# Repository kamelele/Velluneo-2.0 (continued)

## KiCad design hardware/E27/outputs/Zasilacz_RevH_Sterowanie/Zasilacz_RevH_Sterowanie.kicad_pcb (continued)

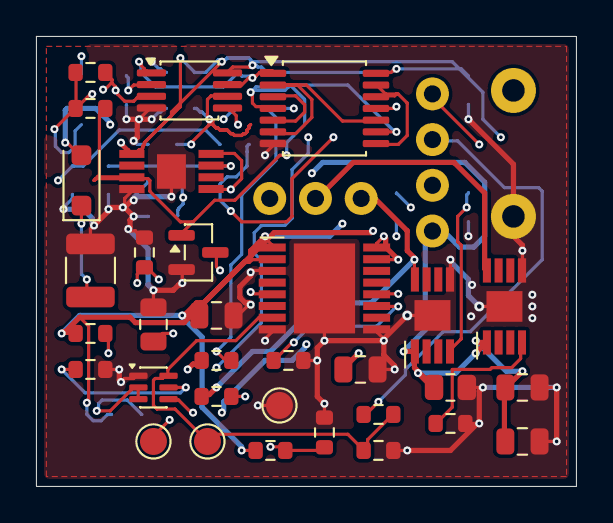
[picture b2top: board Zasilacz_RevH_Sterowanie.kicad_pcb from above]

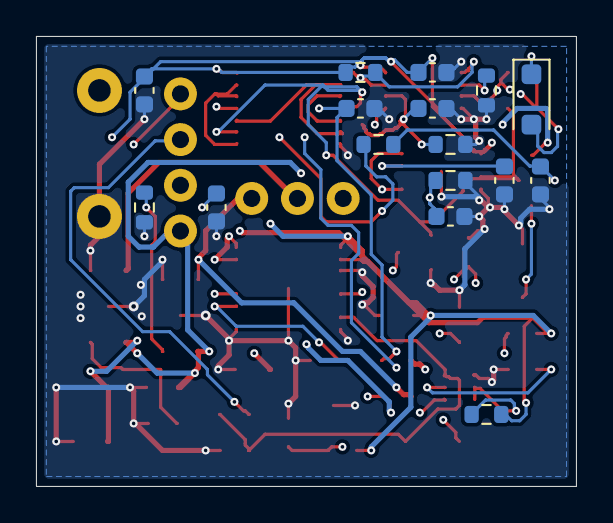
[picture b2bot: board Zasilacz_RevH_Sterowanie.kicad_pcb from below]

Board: 4 copper layers, 30.0 x 25.0 mm, 51 parts (16 on the bottom side), 29 nets.

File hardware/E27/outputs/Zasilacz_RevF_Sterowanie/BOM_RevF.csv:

Ref,Wartość,MPN,Footprint,LCSC Part #,Źródło
U2,TPS26600PWPR,TPS26600PWPR,E27:PWP0016A,C544399,https://jlcpcb.com/partdetail/TexasInstruments-TPS26600PWPR/C544399
C11,100n / 50V,GRM21BR71H104KA01L,Capacitor_SMD:C_0805_2012Metric,C77082,https://jlcpcb.com/partdetail/MurataElectronics-GRM21BR71H10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
R14,226k 0.1%,ERA-3AEB2263V,Resistor_SMD:R_0603_1608Metric,C2075582,https://www.lcsc.com/product-detail/C2075582.html
R15,10k 0.1%,ERA-3AEB103V,Resistor_SMD:R_0603_1608Metric,C190610,https://jlcpcb.com/partdetail/PANASONIC-ERA3AEB103V/C190610
R16,30.1k 1%,ERJ-3EKF3012V,Resistor_SMD:R_0603_1608Metric,C403145,https://www.lcsc.com/product-detail/C403145.html
C12,47n,CC0603KRX7R9BB473,Capacitor_SMD:C_0603_1608Metric,C107093,https://www.lcsc.com/product-detail/C107093.html
R17,10k,ERJ-3EKF1002V,Resistor_SMD:R_0603_1608Metric,C191124,https://www.lcsc.com/product-detail/C191124.html
R18,10k,ERJ-3EKF1002V,Resistor_SMD:R_0603_1608Metric,C191124,https://www.lcsc.com/product-detail/C191124.html
R19,10k,ERJ-6ENF1002V,Resistor_SMD:R_0805_2012Metric,C169253,https://www.lcsc.com/product-detail/C169253.html
C13,100n / 50V,GRM21BR71H104KA01L,Capacitor_SMD:C_0805_2012Metric,C77082,https://jlcpcb.com/partdetail/MurataElectronics-GRM21BR71H10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
J2,S1+TH / S2,,E27:Harness_4pos,,
J3,A+ / KA / KB,,E27:Harness_3pos,,
U3,AL5812MP-13,AL5812MP-13,E27:E27_Al5812_MSOP,C460648,https://www.lcsc.com/product-detail/C460648.html
R20,5.90k 1%,ERJ-3EKF5901V,Resistor_SMD:R_0603_1608Metric,C403290,https://www.lcsc.com/product-detail/C403290.html
C14,100n / 50V,GRM21BR71H104KA01L,Capacitor_SMD:C_0805_2012Metric,C77082,https://jlcpcb.com/partdetail/MurataElectronics-GRM21BR71H10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
U4,AL5812MP-13,AL5812MP-13,E27:E27_Al5812_MSOP,C460648,https://www.lcsc.com/product-detail/C460648.html
R21,5.90k 1%,ERJ-3EKF5901V,Resistor_SMD:R_0603_1608Metric,C403290,https://www.lcsc.com/product-detail/C403290.html
C15,100n / 50V,GRM21BR71H104KA01L,Capacitor_SMD:C_0805_2012Metric,C77082,https://jlcpcb.com/partdetail/MurataElectronics-GRM21BR71H10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
J102,26 V / RTN,,E27:Harness_26V_RTN,,
U101,TPS7A1633,TPS7A1633DGNR,E27:TPS7A16_DGN,C181239,https://www.lcsc.com/product-detail/C181239.html
U102,TLV1702,TLV1702AIDGKR,Package_SO:MSOP-8_3x3mm_P0.65mm,C2870937,https://jlcpcb.com/partdetail/TexasInstruments-TLV1702AIDGKR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
U103,74LVC132A,"74LVC132APW,118",Package_SO:TSSOP-14_4.4x5mm_P0.65mm,C548102,https://jlcpcb.com/partdetail/Nexperia-74LVC132APW118/C548102
D102,PMEG6010CEH,PMEG6010CEH-QX,Diode_SMD:D_SOD-123F,C5311567,https://www.lcsc.com/product-detail/C5311567.html
D103,PMEG6010CEH,PMEG6010CEH-QX,Diode_SMD:D_SOD-123F,C5311567,https://www.lcsc.com/product-detail/C5311567.html
R101,22k,ERJ-3EKF2202V,Resistor_SMD:R_0603_1608Metric,C278611,https://www.lcsc.com/product-detail/C278611.html
R102,2.2k,ERJ-3EKF2201V,Resistor_SMD:R_0603_1608Metric,C116387,https://jlcpcb.com/partdetail/PANASONIC-ERJ3EKF2201V/C116387
R103,133k 0.1%,ERA-3AEB1333V,Resistor_SMD:R_0603_1608Metric,C2087399,https://www.lcsc.com/product-detail/C2087399.html
R104,22k 0.1%,ERA-3AEB223V,Resistor_SMD:R_0603_1608Metric,C445636,https://www.lcsc.com/product-detail/C445636.html
R105,330k 0.1%,RT0603BRD07330KL,Resistor_SMD:R_0603_1608Metric,C861327,https://www.lcsc.com/product-detail/C861327.html
R106,22k 0.1%,ERA-3AEB223V,Resistor_SMD:R_0603_1608Metric,C445636,https://www.lcsc.com/product-detail/C445636.html
R107,330k 0.1%,RT0603BRD07330KL,Resistor_SMD:R_0603_1608Metric,C861327,https://www.lcsc.com/product-detail/C861327.html
R108,22k 0.1%,ERA-3AEB223V,Resistor_SMD:R_0603_1608Metric,C445636,https://www.lcsc.com/product-detail/C445636.html
R109,22k,ERJ-3EKF2202V,Resistor_SMD:R_0603_1608Metric,C278611,https://www.lcsc.com/product-detail/C278611.html
R110,10k 1%,ERJ-3EKF1002V,Resistor_SMD:R_0603_1608Metric,C191124,https://www.lcsc.com/product-detail/C191124.html
R111,100k 1%,ERJ-3EKF1003V,Resistor_SMD:R_0603_1608Metric,C189597,https://www.lcsc.com/product-detail/C189597.html
R112,100k 1%,ERJ-3EKF1003V,Resistor_SMD:R_0603_1608Metric,C189597,https://www.lcsc.com/product-detail/C189597.html
C101,2.2u / 100V,C3225X7R2A225K230AB,Capacitor_SMD:C_1210_3225Metric,C2167827,https://www.lcsc.com/product-detail/C2167827.html
C102,10u / 25V,GRM21BC71E106KE11L,Capacitor_SMD:C_0805_2012Metric,C109040,https://www.lcsc.com/product-detail/C109040.html
C103,10n,CC0603KRX7R9BB103,Capacitor_SMD:C_0603_1608Metric,C100042,https://www.lcsc.com/product-detail/C100042.html
C104,220n / 50V X7R 10%,CGA3E3X7R1H224K080AE,Capacitor_SMD:C_0603_1608Metric,C2171795,https://jlcpcb.com/partdetail/TDK-CGA3E3X7R1H224K080AE/C2171795
C105,220n / 50V X7R 10%,CGA3E3X7R1H224K080AE,Capacitor_SMD:C_0603_1608Metric,C2171795,https://jlcpcb.com/partdetail/TDK-CGA3E3X7R1H224K080AE/C2171795
C106,10n,CC0603KRX7R9BB103,Capacitor_SMD:C_0603_1608Metric,C100042,https://www.lcsc.com/product-detail/C100042.html
C107,100n,C1608X7R1H104K080AE,Capacitor_SMD:C_0603_1608Metric,C2167477,https://jlcpcb.com/partdetail/TDK-C1608X7R1H104K080AE/C2167477
C108,10n,CC0603KRX7R9BB103,Capacitor_SMD:C_0603_1608Metric,C100042,https://www.lcsc.com/product-detail/C100042.html
C109,100n,C1608X7R1H104K080AE,Capacitor_SMD:C_0603_1608Metric,C2167477,https://jlcpcb.com/partdetail/TDK-C1608X7R1H104K080AE/C2167477
R113,100k 1%,ERJ-3EKF1003V,Resistor_SMD:R_0603_1608Metric,C189597,https://www.lcsc.com/product-detail/C189597.html
Q101,MMDT3904,MMDT3904-7-F,Package_TO_SOT_SMD:SOT-363_SC-70-6,C83572,https://www.lcsc.com/product-detail/C83572.html
Q102,2N7002BK,"2N7002BK,215",Package_TO_SOT_SMD:SOT-23,C282405,https://www.lcsc.com/product-detail/C282405.html

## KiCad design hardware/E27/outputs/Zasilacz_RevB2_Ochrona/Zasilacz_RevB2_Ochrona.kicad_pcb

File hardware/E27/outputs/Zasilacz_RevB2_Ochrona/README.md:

# E27 · Rev B2 · moduł prób ochrony zwarciowej

Moduł **50 × 30 mm** do badań części wtórnej zasilacza Rev B1 z izolowanego źródła **18–30 V DC**. Dwa detektory mierzą napięcie na regulatorach prądu. Po wykryciu nadmiernego spadku na jednym z nich przerzutnik utrzymuje blokadę obu kanałów, dopóki układ pomocniczy jest zasilany. Moduł włącza się w powrót S1/TH1 do SHDN.

[Projekt KiCad](Zasilacz_RevB2_Ochrona.kicad_pro) · [Schemat](Zasilacz_RevB2_Ochrona.kicad_sch) · [PCB](Zasilacz_RevB2_Ochrona.kicad_pcb) · [BOM](BOM_RevB2.csv) · [Pliki do przeglądu](Produkcja_DO_PRZEGLADU)

[Schemat do podglądu](Podglady/Zasilacz_RevB2_Ochrona.svg) · [Spód PCB](Podglady/RevB2_dol_3D.png)

## 1. Problem i próg

Przy zwarciu obciążenia AL5812 może nadal ograniczać prąd do około 127 mA. Przy 26 V na regulatorze oznacza to w pierwszej chwili **około 3,3 W**, podczas gdy prąd całego zasilacza może pozostać poniżej progu nadprądowego eFuse. Napięcie K1 lub K2 względem S_RTN odpowiada spadkowi na odpowiednim AL5812, więc mierzymy je niezależnie od prądu eFuse. [Diodes AL5812](https://www.diodes.com/datasheet/download/AL5812.pdf) · [TI TPS26600](https://www.ti.com/lit/ds/symlink/tps2660.pdf)

TLV1702 porównuje napięcie z dzielników 330 kΩ / 22 kΩ z odniesieniem z 3,3 V przez 133 kΩ / 22 kΩ. Kondensatory 220 nF dają około **4,54 ms** nominalnej stałej czasowej. W modelu przyjęto ±27% efektywnej pojemności. Próg nominalny na K1/K2 to **7,49 V**, a model narożnikowy daje **7,15–7,85 V**. Uwzględniono ±2% szyny, ±0,35% osobno dla każdego rezystora, ±5,5 mV offsetu i prądy polaryzacji komparatorów. Tolerancja rezystorów obejmuje ±0,1% początkowo i ±25 ppm/K dla przyjętej zmiany temperatury o 100 K. Dla badanego punktu 26,4 V z obciążeniem 20 V pozostaje około 0,75 V do najniższego obliczonego progu, przed tętnieniami. [TI TLV1702](https://www.ti.com/lit/ds/symlink/tlv1702.pdf) · [TI TPS7A16](https://www.ti.com/lit/ds/symlink/tps7a16.pdf) · [Panasonic ERA 133 kΩ](https://industrial.panasonic.com/ww/products/pt/high-precision-chip-resistors/models/ERA3AEB1333V)

## 2. Sekwencja i współpraca z Rev B1

- TPS7A1633 zasila układ i wystawia sygnał PG po opóźnieniu, typowo około 12 ms dla 10 nF. Zbocze zegara przerzutnika SN74HCS74 jest dodatkowo opóźnione przez RC. PG przez D1 oraz wyjścia komparatora mogą wymusić niski CLR_N. PG i wyjście PERMIT wspólnie sterują PhotoMOS przez bramkę Schmitta. Przed pierwszym załączeniem weryfikować poziomy PG, CLK, CLR_N oraz stan PhotoMOS na wolnych i szybkich rampach. [TI TPS7A16](https://www.ti.com/lit/ds/symlink/tps7a16.pdf) · [TI SN74HCS74](https://www.ti.com/lit/ds/symlink/sn74hcs74.pdf) · [TI SN74LVC1G132](https://www.ti.com/lit/ds/symlink/sn74lvc1g132.pdf)
- Po zdarzeniu niskie CLR_N zeruje PERMIT. Powrót K1/K2 do normalnych wartości ani ponowne zamknięcie S1 nie daje nowego zbocza CLK. Odcięcie utrzymuje się do resetu PG. Głęboki zanik szyny, po którym PG ponownie wzrośnie, może sam ponownie uzbroić układ. To zachowanie jest jawnie objęte próbą.
- PhotoMOS otwiera powrót S1/TH1. Na Rev B1 rezystor R18 ściąga SHDN w dół. R12 modułu dodaje 100 kΩ do istniejących R17/R18, po 10 kΩ, co daje **około 2,17 V** przy 26 V oraz **1,50–2,50 V** przy 18–30 V w modelu bez prądu wejścia SHDN. Bez R12 sam dzielnik daje ok. 13 V przy 26 V. Zalecany zakres wejścia według TI to 0–4 V. Sprawdzić rzeczywiste napięcia oraz pracę styków S1 przy zmniejszonym prądzie. [TI TPS26600, zalecane warunki pracy i opis SHDN](https://www.ti.com/lit/ds/symlink/tps2660.pdf)

### Wiązka J1

1. **S_RAW** z regulowanej szyny przed eFuse.
2. **S_RTN** z masy wtórnej eFuse i regulatorów.
3. **K1** z wyjścia pierwszego regulatora.
4. **K2** z wyjścia drugiego regulatora.
5. **S1_RETURN** z powrotu zamkniętej pętli S1/TH1. Odłączyć ją uprzednio od J2-2.
6. **S_EN** do J2-2 Rev B1. R17 i R18 w tym zestawie mają wartości z Rev B1. S2 i istniejące zabezpieczenie OVP pracują w swoich dotychczasowych torach.

Punkty TP1–TP6 oznaczają odpowiednio S_RTN, 3,3 V, PG, CLR_N, PERMIT i SHDN. Pomiar CLK można wykonać na C8. D3 jest diodą od wyjścia LDO do odseparowanego przez D2 wejścia LDO, która ogranicza napięcie wsteczne przy zaniku. Przy próbach zaniku sprawdzić również (V_{OUT}-V_{IN}) U1 przy rzeczywistych pojemnościach i temperaturze. Dla C2 10 µF dobrać egzemplarz o pojemności efektywnej co najmniej 2,2 µF przy polaryzacji 3,3 V i skrajnej temperaturze. [TI TPS7A16](https://www.ti.com/lit/ds/symlink/tps7a16.pdf) · [TDK C1](https://product.tdk.com/en/search/capacitor/ceramic/mlcc/info?part_no=C3225X7R2A225K230AB)

## 3. Model i wynik kontroli

- Model RC przewiduje decyzję komparatora po **1,06–2,08 ms** dla idealnego skoku 0→26 V i **4,14–8,88 ms** dla 0→10 V. Czas odłączenia prądu obejmuje dodatkowo PhotoMOS, TPS26600 i rozładowanie pojemności. Panasonic podaje do 0,5 ms wyłączenia AQY212GS w swoich warunkach 25°C, z prądem wejścia 5 mA i obciążeniem 100 mA. W pętli SHDN warunki są inne. [Panasonic AQY212GS](https://industry.panasonic.com/ac/cdn/e/control/relay/photomos/catalog/semi_eng_gu1a_aqy21_gs.pdf)
- [Wyniki 18 przypadków modelowych](Model_RevB2_przypadki.csv) obejmują dwa narożniki, zwarcia osobno na K1 i K2, zwarcie przy włączeniu, impulsy, otwartą pętlę S1 i ponowne uzbrojenie po utracie PG. Wydłużenie filtra z początkowych 47 nF do 220 nF pozwoliło w obu badanych narożnikach odrzucić pojedynczy impuls 100 µs do 26 V przy początkowych 6,4 V na kanale. Impuls 500 µs w tych samych warunkach wyzwolił odcięcie. Model stanów pomija fizykę półprzewodników, opóźnienie TPS26600 i termikę.
- [Raport ERC](ERC.rpt) i [raport DRC z porównaniem schematu](DRC.rpt) wykazały zero naruszeń oraz zero niepołączonych padów. Dodatkowe sprawdzenie porównało 102 przypisania pin–sieć w generatorze, schemacie i PCB, 31 pozycji BOM i 30 pozycji montażu SMD. Nie wykonano prób fizycznych.

## 4. Próby na stanowisku DC

1. Uruchomić moduł samodzielnie, bez strony sieciowej i bez zasilania obciążenia. Zmierzyć 3,3 V, VREF, PG, CLK i CLR_N na zimnym oraz nagrzanym module. Zmierzyć upływ PhotoMOS oraz potwierdzić otwarcie między pinami 5 i 6 przy braku zasilania. Zbadać szybkie i wolne narastanie oraz zapady, także w okolicy dolnych granic pracy logiki.
2. Podać na K1 i K2 oddzielnie kontrolowaną rampę względem S_RTN. Potwierdzić próg, czas od skoku do CLR_N i utrzymanie blokady po usunięciu przyczyny. Przy skokach mierzyć też czas otwarcia PhotoMOS i odcięcia prądu przez eFuse. Próby powtórzyć przy obu kanałach oraz przy rozłączaniu S1 i S2.
3. Połączyć z częścią wtórną Rev B1 zasilaną z izolowanego źródła 26 V z ograniczeniem prądu. Rozpocząć od dwóch obciążeń zastępczych. Zmierzyć SHDN w obu stanach, minimalny spadek na obciążeniu i prąd obu kanałów. Dopiero potem przejść do osobnych zwarć o ograniczonej energii, początkowo krótkich. Rejestrować A+, K1, K2, CLR_N, SHDN oraz prąd i temperaturę regulatorów.
4. Sprawdzić temperaturę przy częściowym zwarciu poniżej progu. Przykładowo 7 V na regulatorze odpowiada około 0,9 W przy 127 mA. Sprawdzić brak przewodu pomiarowego, przekaźnik pozostający w zwarciu oraz spadek i powrót PG. Sam przerwany przewód pomiarowy pozostawia kanał bez detekcji nadmiernego napięcia.

Moduł jest osobną płytką laboratoryjną, ze stratą LDO szacowaną na około 0,22 W przy 26 V i załączonym PhotoMOS. Po pomiarach można ocenić, ile z układu trzeba przenieść na główną płytkę i czy pobór prądu jest akceptowalny.

Do odtworzenia etapu służy `work/export_b2.ps1` uruchamiany z katalogu `hardware/E27`. Zapisuje projekt, wyniki modelu, kontrole i eksporty KiCad.

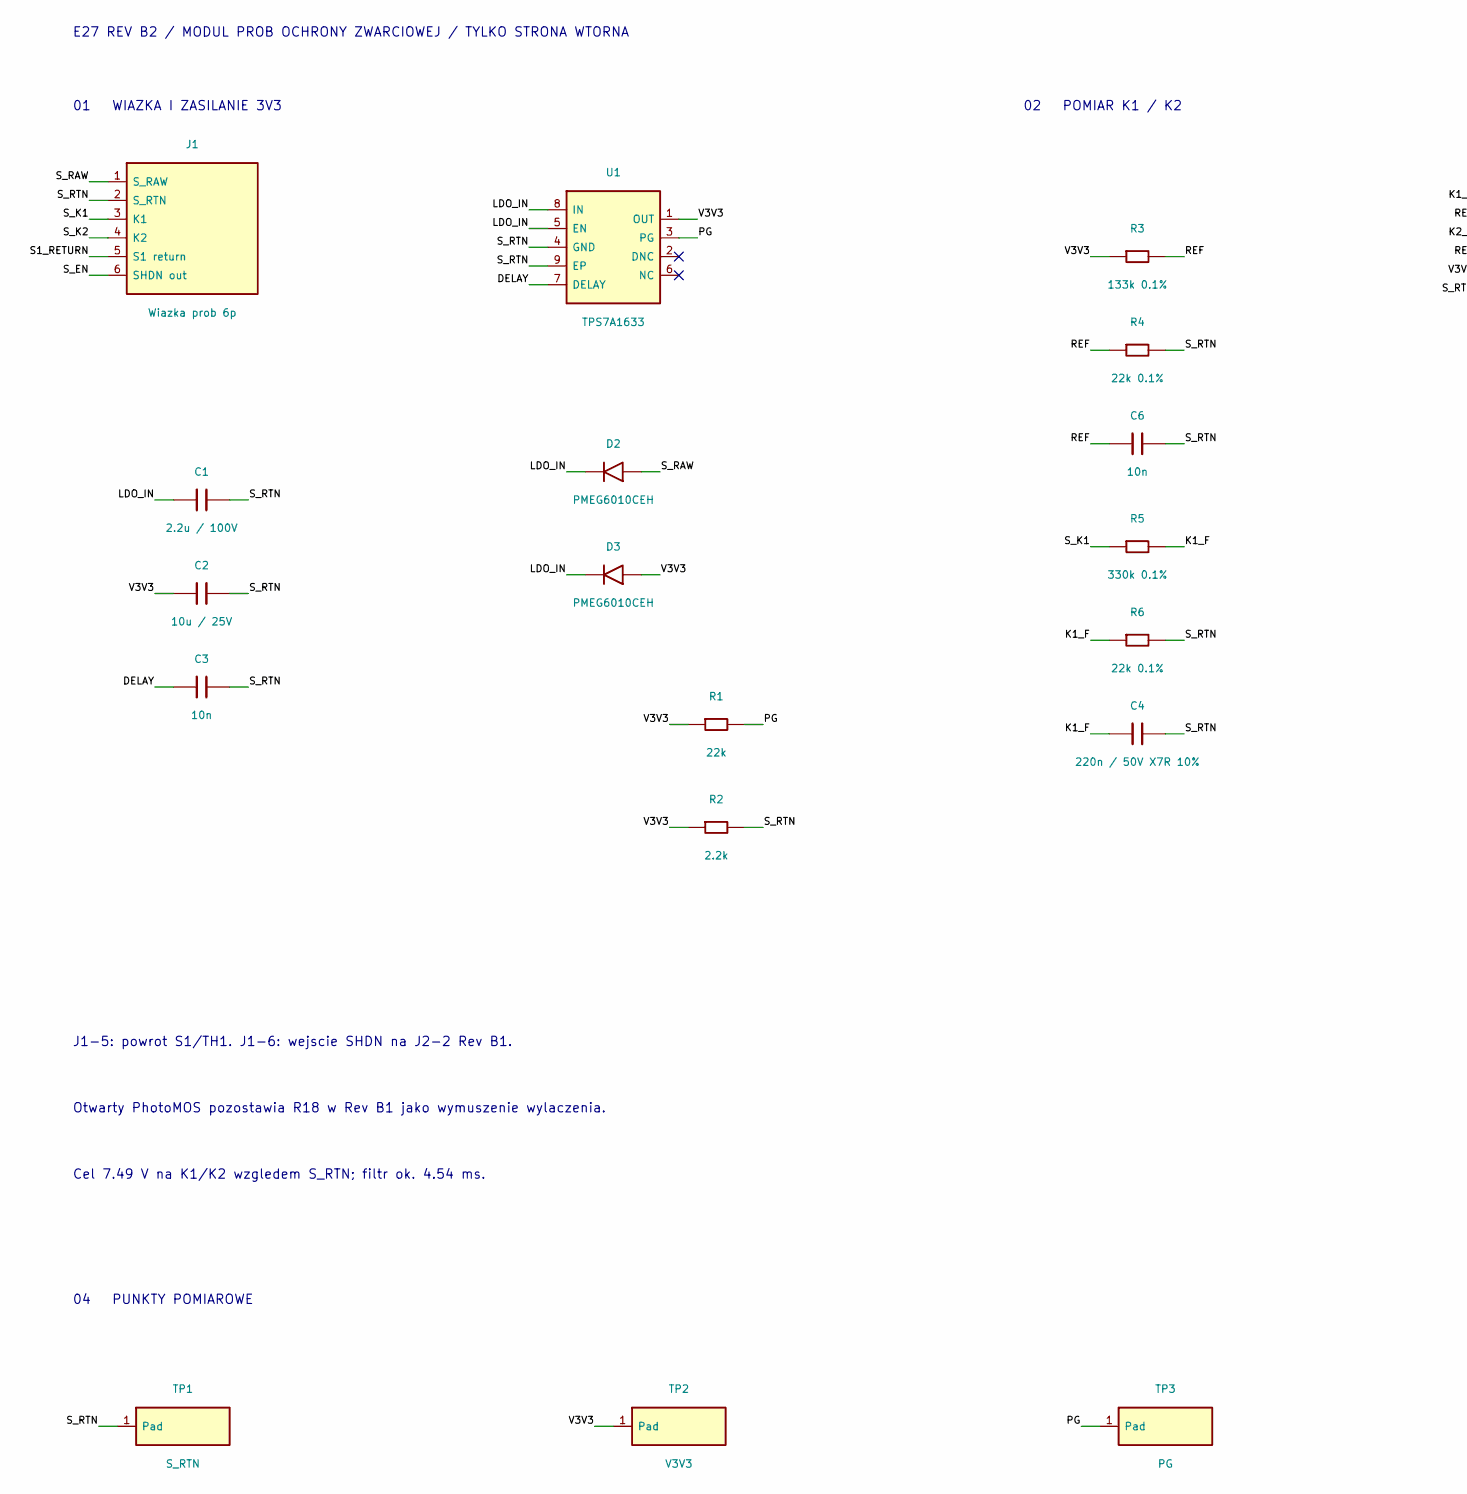
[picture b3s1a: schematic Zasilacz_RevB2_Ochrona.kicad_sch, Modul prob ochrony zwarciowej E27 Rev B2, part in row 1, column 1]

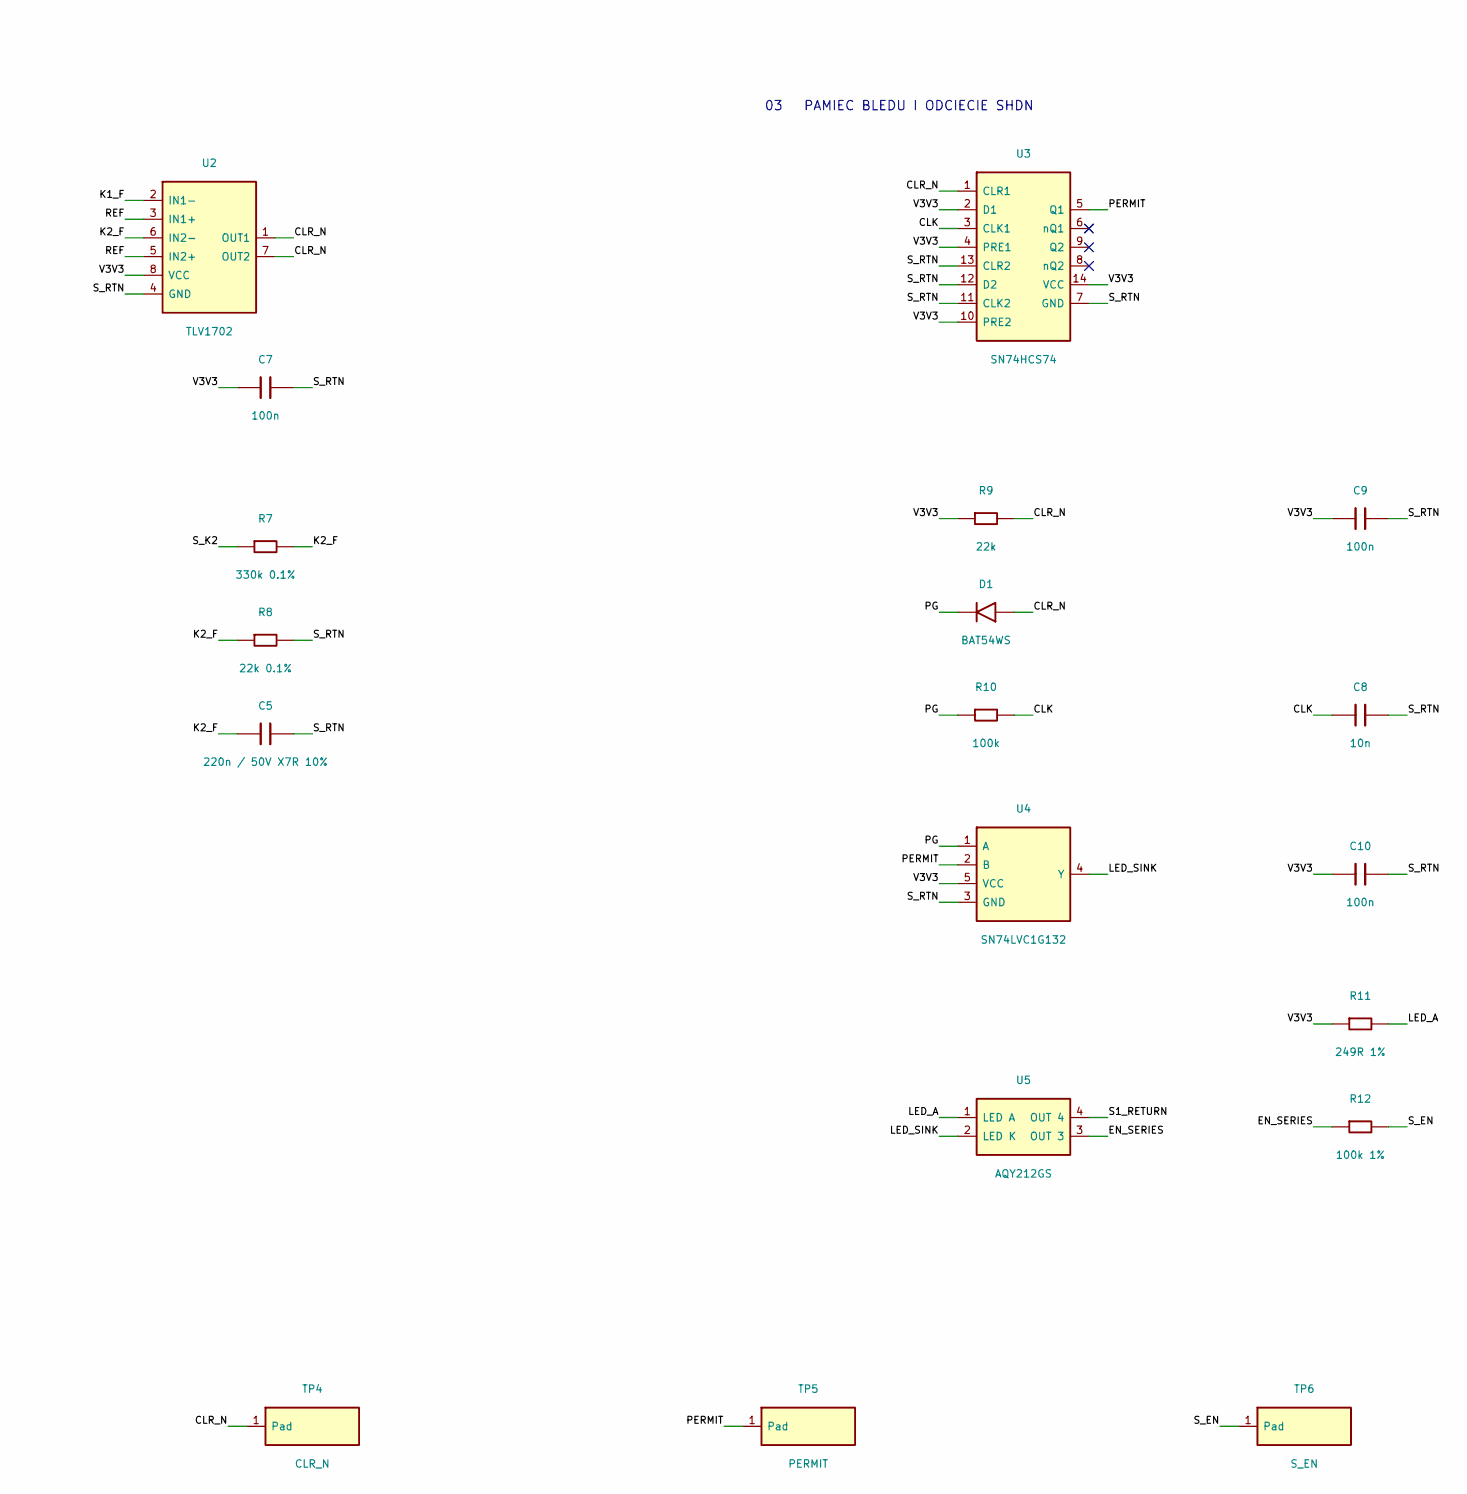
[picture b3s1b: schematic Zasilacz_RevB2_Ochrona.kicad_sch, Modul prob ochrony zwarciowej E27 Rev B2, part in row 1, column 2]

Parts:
C1: 2.2u / 100V; C_1210_3225Metric
C2: 10u / 25V; C_0805_2012Metric
C3, C6, C8: 10n; C_0603_1608Metric
C4, C5: 220n / 50V X7R 10%; C_0603_1608Metric
C7, C9, C10: 100n; C_0603_1608Metric
D1: BAT54WS; D_SOD-323
D2, D3: PMEG6010CEH; D_SOD-123F
J1: Wiazka prob 6p; JST_XH_B6B-XH-A_1x06_P2.50mm_Vertical
R1, R9: 22k; R_0603_1608Metric
R2: 2.2k; R_0603_1608Metric
R3: 133k 0.1%; R_0603_1608Metric
R4, R6, R8: 22k 0.1%; R_0603_1608Metric
R5, R7: 330k 0.1%; R_0603_1608Metric
R10: 100k; R_0603_1608Metric
R11: 249R 1%; R_0603_1608Metric
R12: 100k 1%; R_0603_1608Metric
TP1: S_RTN; TestPoint_Pad_D1.5mm
TP2: V3V3; TestPoint_Pad_D1.5mm
TP3: PG; TestPoint_Pad_D1.5mm
TP4: CLR_N; TestPoint_Pad_D1.5mm
TP5: PERMIT; TestPoint_Pad_D1.5mm
TP6: S_EN; TestPoint_Pad_D1.5mm
U1: TPS7A1633; TPS7A16_DGN
U2: TLV1702; MSOP-8_3x3mm_P0.65mm
U3: SN74HCS74; TSSOP-14_4.4x5mm_P0.65mm
U4: SN74LVC1G132; SOT-23-5
U5: AQY212GS; AQY212GS_SOP4

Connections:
/CLK: C8.1, R10.2, U3.3 (CLK1)
/CLR_N: D1.2 (A), R9.2, TP4.1, U2.1 (OUT1), U2.7 (OUT2), U3.1 (CLR1)
/DELAY: C3.1, U1.7 (DELAY)
/EN_SERIES: R12.1, U5.3 (OUT 3)
/K1_F: C4.1, R5.2, R6.1, U2.2 (IN1-)
/K2_F: C5.1, R7.2, R8.1, U2.6 (IN2-)
/LDO_IN: C1.1, D2.1 (K), D3.1 (K), U1.5 (EN), U1.8 (IN)
/LED_A: R11.2, U5.1 (LED A)
/LED_SINK: U4.4 (Y), U5.2 (LED K)
/PERMIT: TP5.1, U3.5 (Q1), U4.2 (B)
/PG: D1.1 (K), R1.2, R10.1, TP3.1, U1.3 (PG), U4.1 (A)
/REF: C6.1, R3.2, R4.1, U2.3 (IN1+), U2.5 (IN2+)
/S1_RETURN: J1.5 (S1 return), U5.4 (OUT 4)
/S_EN: J1.6 (SHDN out), R12.2, TP6.1
/S_K1: J1.3 (K1), R5.1
/S_K2: J1.4 (K2), R7.1
/S_RAW: D2.2 (A), J1.1 (S_RAW)
/S_RTN: C1.2, C2.2, C3.2, C4.2, C5.2, C6.2, C7.2, C8.2, C9.2, C10.2, J1.2 (S_RTN), R2.2, R4.2, R6.2, R8.2, TP1.1, U1.4 (GND), U1.9 (EP), U2.4 (GND), U3.7 (GND), U3.11 (CLK2), U3.12 (D2), U3.13 (CLR2), U4.3 (GND)
/V3V3: C2.1, C7.1, C9.1, C10.1, D3.2 (A), R1.1, R2.1, R3.1, R9.1, R11.1, TP2.1, U1.1 (OUT), U2.8 (VCC), U3.2 (D1), U3.4 (PRE1), U3.10 (PRE2), U3.14 (VCC), U4.5 (VCC)

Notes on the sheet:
E27 REV B2 / MODUL PROB OCHRONY ZWARCIOWEJ / TYLKO STRONA WTORNA
01 WIAZKA I ZASILANIE 3V3
02 POMIAR K1 / K2
03 PAMIEC BLEDU I ODCIECIE SHDN
04 PUNKTY POMIAROWE
J1-5: powrot S1/TH1. J1-6: wejscie SHDN na J2-2 Rev B1.
Otwarty PhotoMOS pozostawia R18 w Rev B1 jako wymuszenie wylaczenia.
Cel 7.49 V na K1/K2 wzgledem S_RTN; filtr ok. 4.54 ms.

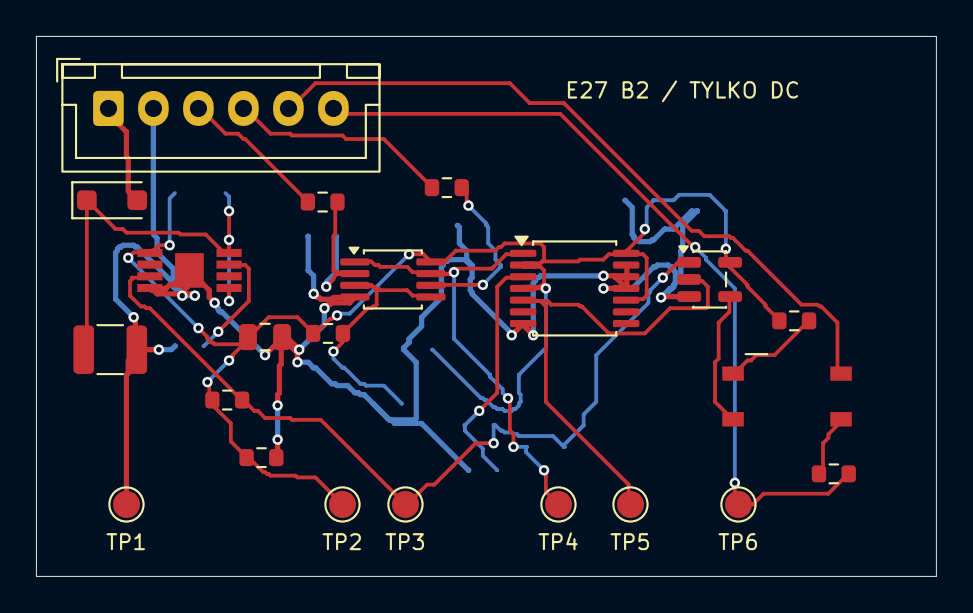
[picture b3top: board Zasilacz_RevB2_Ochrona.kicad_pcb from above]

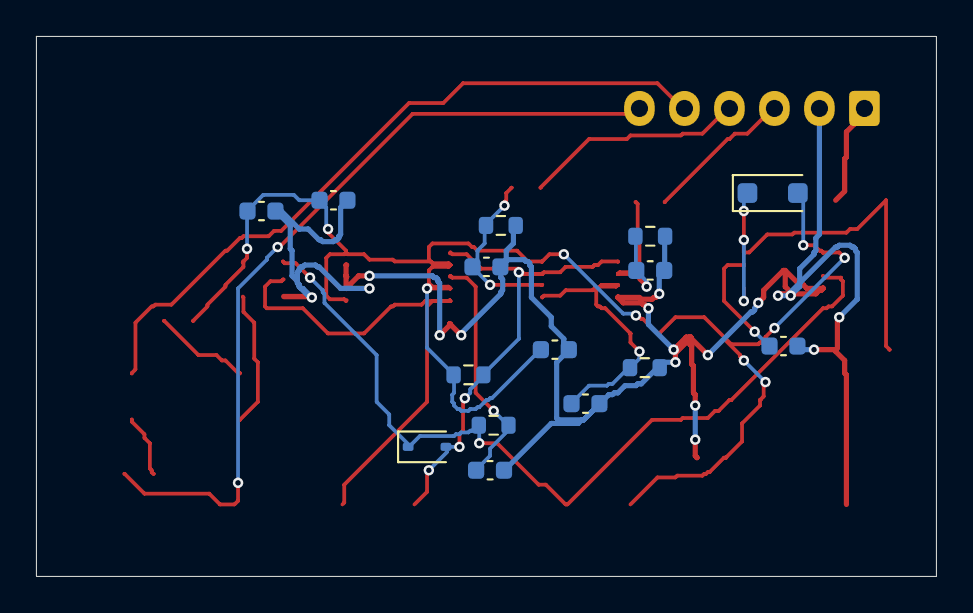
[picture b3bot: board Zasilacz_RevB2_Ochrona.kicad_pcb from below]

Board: 2 copper layers, 50.0 x 30.0 mm, 37 parts (15 on the bottom side), 19 nets.

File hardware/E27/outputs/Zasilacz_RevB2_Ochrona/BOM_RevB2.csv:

Ref,Wartość,MPN,Footprint
J1,Wiazka prob 6p,B6B-XH-A(LF)(SN),Connector_JST:JST_XH_B6B-XH-A_1x06_P2.50mm_Vertical
U1,TPS7A1633,TPS7A1633DGNR,E27:TPS7A16_DGN
U2,TLV1702,TLV1702AIDGKR,Package_SO:MSOP-8_3x3mm_P0.65mm
U3,SN74HCS74,SN74HCS74PWR,Package_SO:TSSOP-14_4.4x5mm_P0.65mm
U4,SN74LVC1G132,SN74LVC1G132DBVR,Package_TO_SOT_SMD:SOT-23-5
U5,AQY212GS,AQY212GS,E27:AQY212GS_SOP4
D1,BAT54WS,BAT54WS,Diode_SMD:D_SOD-323
D2,PMEG6010CEH,"PMEG6010CEH,115",Diode_SMD:D_SOD-123F
D3,PMEG6010CEH,"PMEG6010CEH,115",Diode_SMD:D_SOD-123F
R1,22k,,Resistor_SMD:R_0603_1608Metric
R2,2.2k,,Resistor_SMD:R_0603_1608Metric
R3,133k 0.1%,ERA-3AEB1333V,Resistor_SMD:R_0603_1608Metric
R4,22k 0.1%,ERA-3AEB223V,Resistor_SMD:R_0603_1608Metric
R5,330k 0.1%,ERA-3AEB3303V,Resistor_SMD:R_0603_1608Metric
R6,22k 0.1%,ERA-3AEB223V,Resistor_SMD:R_0603_1608Metric
R7,330k 0.1%,ERA-3AEB3303V,Resistor_SMD:R_0603_1608Metric
R8,22k 0.1%,ERA-3AEB223V,Resistor_SMD:R_0603_1608Metric
R9,22k,,Resistor_SMD:R_0603_1608Metric
R10,100k,,Resistor_SMD:R_0603_1608Metric
R11,249R 1%,,Resistor_SMD:R_0603_1608Metric
R12,100k 1%,,Resistor_SMD:R_0603_1608Metric
C1,2.2u / 100V,C3225X7R2A225K230AB,Capacitor_SMD:C_1210_3225Metric
C2,10u / 25V,GRM21BC71E106KE11L,Capacitor_SMD:C_0805_2012Metric
C3,10n,,Capacitor_SMD:C_0603_1608Metric
C4,220n / 50V X7R 10%,,Capacitor_SMD:C_0603_1608Metric
C5,220n / 50V X7R 10%,,Capacitor_SMD:C_0603_1608Metric
C6,10n,,Capacitor_SMD:C_0603_1608Metric
C7,100n,,Capacitor_SMD:C_0603_1608Metric
C8,10n,,Capacitor_SMD:C_0603_1608Metric
C9,100n,,Capacitor_SMD:C_0603_1608Metric
C10,100n,,Capacitor_SMD:C_0603_1608Metric

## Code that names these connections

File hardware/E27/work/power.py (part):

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    add('C2','15u / 450V','Capacitor_THT:CP_Radial_D10.0mm_P5.00mm','P_BULK P_0',(17.6,12.5),(111.76,81.28),'CP',90,part='450BXF15M10X20',maker='Rubycon',function='Magazyn energii na szynie HV')
    add('R2','510k HV',R20,'P_BULK P_BLEED',(20.8,4.2),(39.37,99.06),'R',part='',function='Rozładowanie szyny HV',notes='Dwa rezystory szeregowe, potwierdzić napięcie pracy, dobrać tolerancję i udar.')
    add('R3','510k HV',R20,'P_BLEED P_0',(20.8,7.9),(76.2,99.06),'R',part='',function='Rozładowanie szyny HV')
    add('T1','EE16 84:23:13','E27:EE16_6pins_RFQ',{1:'P_D',2:'P_BULK',3:'P_AUX',4:'P_0',5:'S_RAW',6:'S_SW'},(BOUNDARY,9.6),(205.74,59.69),'T',part='',function='Transformator flyback 1.2 mH ±8%',notes='RFQ. Potwierdzić karkas, pinout, TIW, odstępy i badania. Zwroty w raporcie.')
    add('C3','1.5n / 200V',C80,'P_CL P_BULK',(24.1,20.2),(176.53,83.82),'C',90,part='08052C152KAT2A',maker='KYOCERA AVX',function='Kondensator ogranicznika RCD')
    add('R4','1M',R12,'P_CL P_BULK',(21.6,20.2),(213.36,83.82),'R',90,part='ERJ-8GEYJ105V',maker='Panasonic',function='Rezystor ogranicznika RCD')
    add('D5','US1J',SMA,'P_CL P_D',(25.25,16.75),(250.19,83.82),'D',part='US1J-13-F',maker='Diodes Inc.',function='Dioda ogranicznika RCD',notes='Potwierdzić impulsy, temperaturę i rzeczywiste VDS.')
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    add('C8','330p',C60,'S_FB S_GND',(43.3,27.75),(369.57,73.66),'C',part='CC0603KRX7R9BB331',maker='Yageo',function='Odprzęganie FB')
    add('C9','2.2u / 25V',C12,'S_BPS S_GND',(43.9,30.25),(288.29,86.36),'C',part='TMK316B7225KL-T',maker='Taiyo Yuden',function='Odprzęganie BPS')
    add('R12','2.2k',R80,'S_RAW S_Z18',(50.4,21.2),(328.93,86.36),'R',part='ERJ-6ENF2201V',maker='Panasonic',function='Prąd polaryzacji zenera VO')
    add('ZD1','18V',SOD,'S_Z18 S_GND',(54.2,23.5),(369.57,86.36),'Z',90,'BZT52C18-7-F','Diodes Inc.','Ograniczenie zasilania pinu VO')
    add('Q1','MMBT5551','Package_TO_SOT_SMD:SOT-23',{1:'S_Z18',2:'S_VO',3:'S_RAW'},(50.9,25.1),(288.29,101.6),'Q',part='MMBT5551LT1G',maker='onsemi',function='Wtórnik zasilający pin VO')
    add('C10','100n / 50V',C80,'S_VO S_GND',(47.5,25.65),(328.93,101.6),'C',90,'GRM21BR71H104KA01L','Murata','Odprzęganie VO')
    add('ZD2','27V',SOD,'S_RAW S_OVA',(52.6,29.4),(369.57,101.6),'Z',part='BZT52C27-7-F',maker='Diodes Inc.',function='Wtórne wykrywanie przepięcia')
    add('R13','100R',R80,'S_OVA S_OVB',(50.0,31.1),(328.93,116.84),'R',part='ERJ-6ENF1000V',maker='Panasonic',function='Ograniczenie prądu wstrzykiwanego do BPS')
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        left=[(3,'AC1'),(4,'AC2')]
        right=[(1,'+'),(2,'-')]
    else:
        labels={'AC':['L','N'],'J3':['A+','KA','KB'],'J4':['S1 feed','SHDN','eFuse out','LED A+']}[kind]
        left=list(enumerate(labels,1))
        right=[]
    half=10.16 if kind in ('LYT','EF') else 7.62 if kind=='J4' else 5.08
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
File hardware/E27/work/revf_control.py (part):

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
def device_from_guard(p):
    return power.Device(ref_name(p.ref),p.value,p.fp,
        {n:{'S_K1':'S_LED_KA','S_K2':'S_LED_KB','CLR_N':'FAULT_N'}.get(net,net) for n,net in p.pins.items()},
        p.xy,p.sch,'G_'+p.kind,p.rotation,p.mpn)


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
